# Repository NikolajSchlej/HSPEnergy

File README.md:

HSP Energy
=========

Hardware project of HS Regensburg

This project of Embedded Systems Laboratory of HS Regensburg 
aims to work out rules and guidelines for energy-effective coding
for different uC families.

There is a base board, where DC-DC, JTAG debugger and USB-UART converter are located, 
and CPU boards for different microcontrollers.

Documentation will be added when ready.

Scematics and layouts made in EagleCAD 6. 
All hardware involved is open and available under terms of copyleft license.

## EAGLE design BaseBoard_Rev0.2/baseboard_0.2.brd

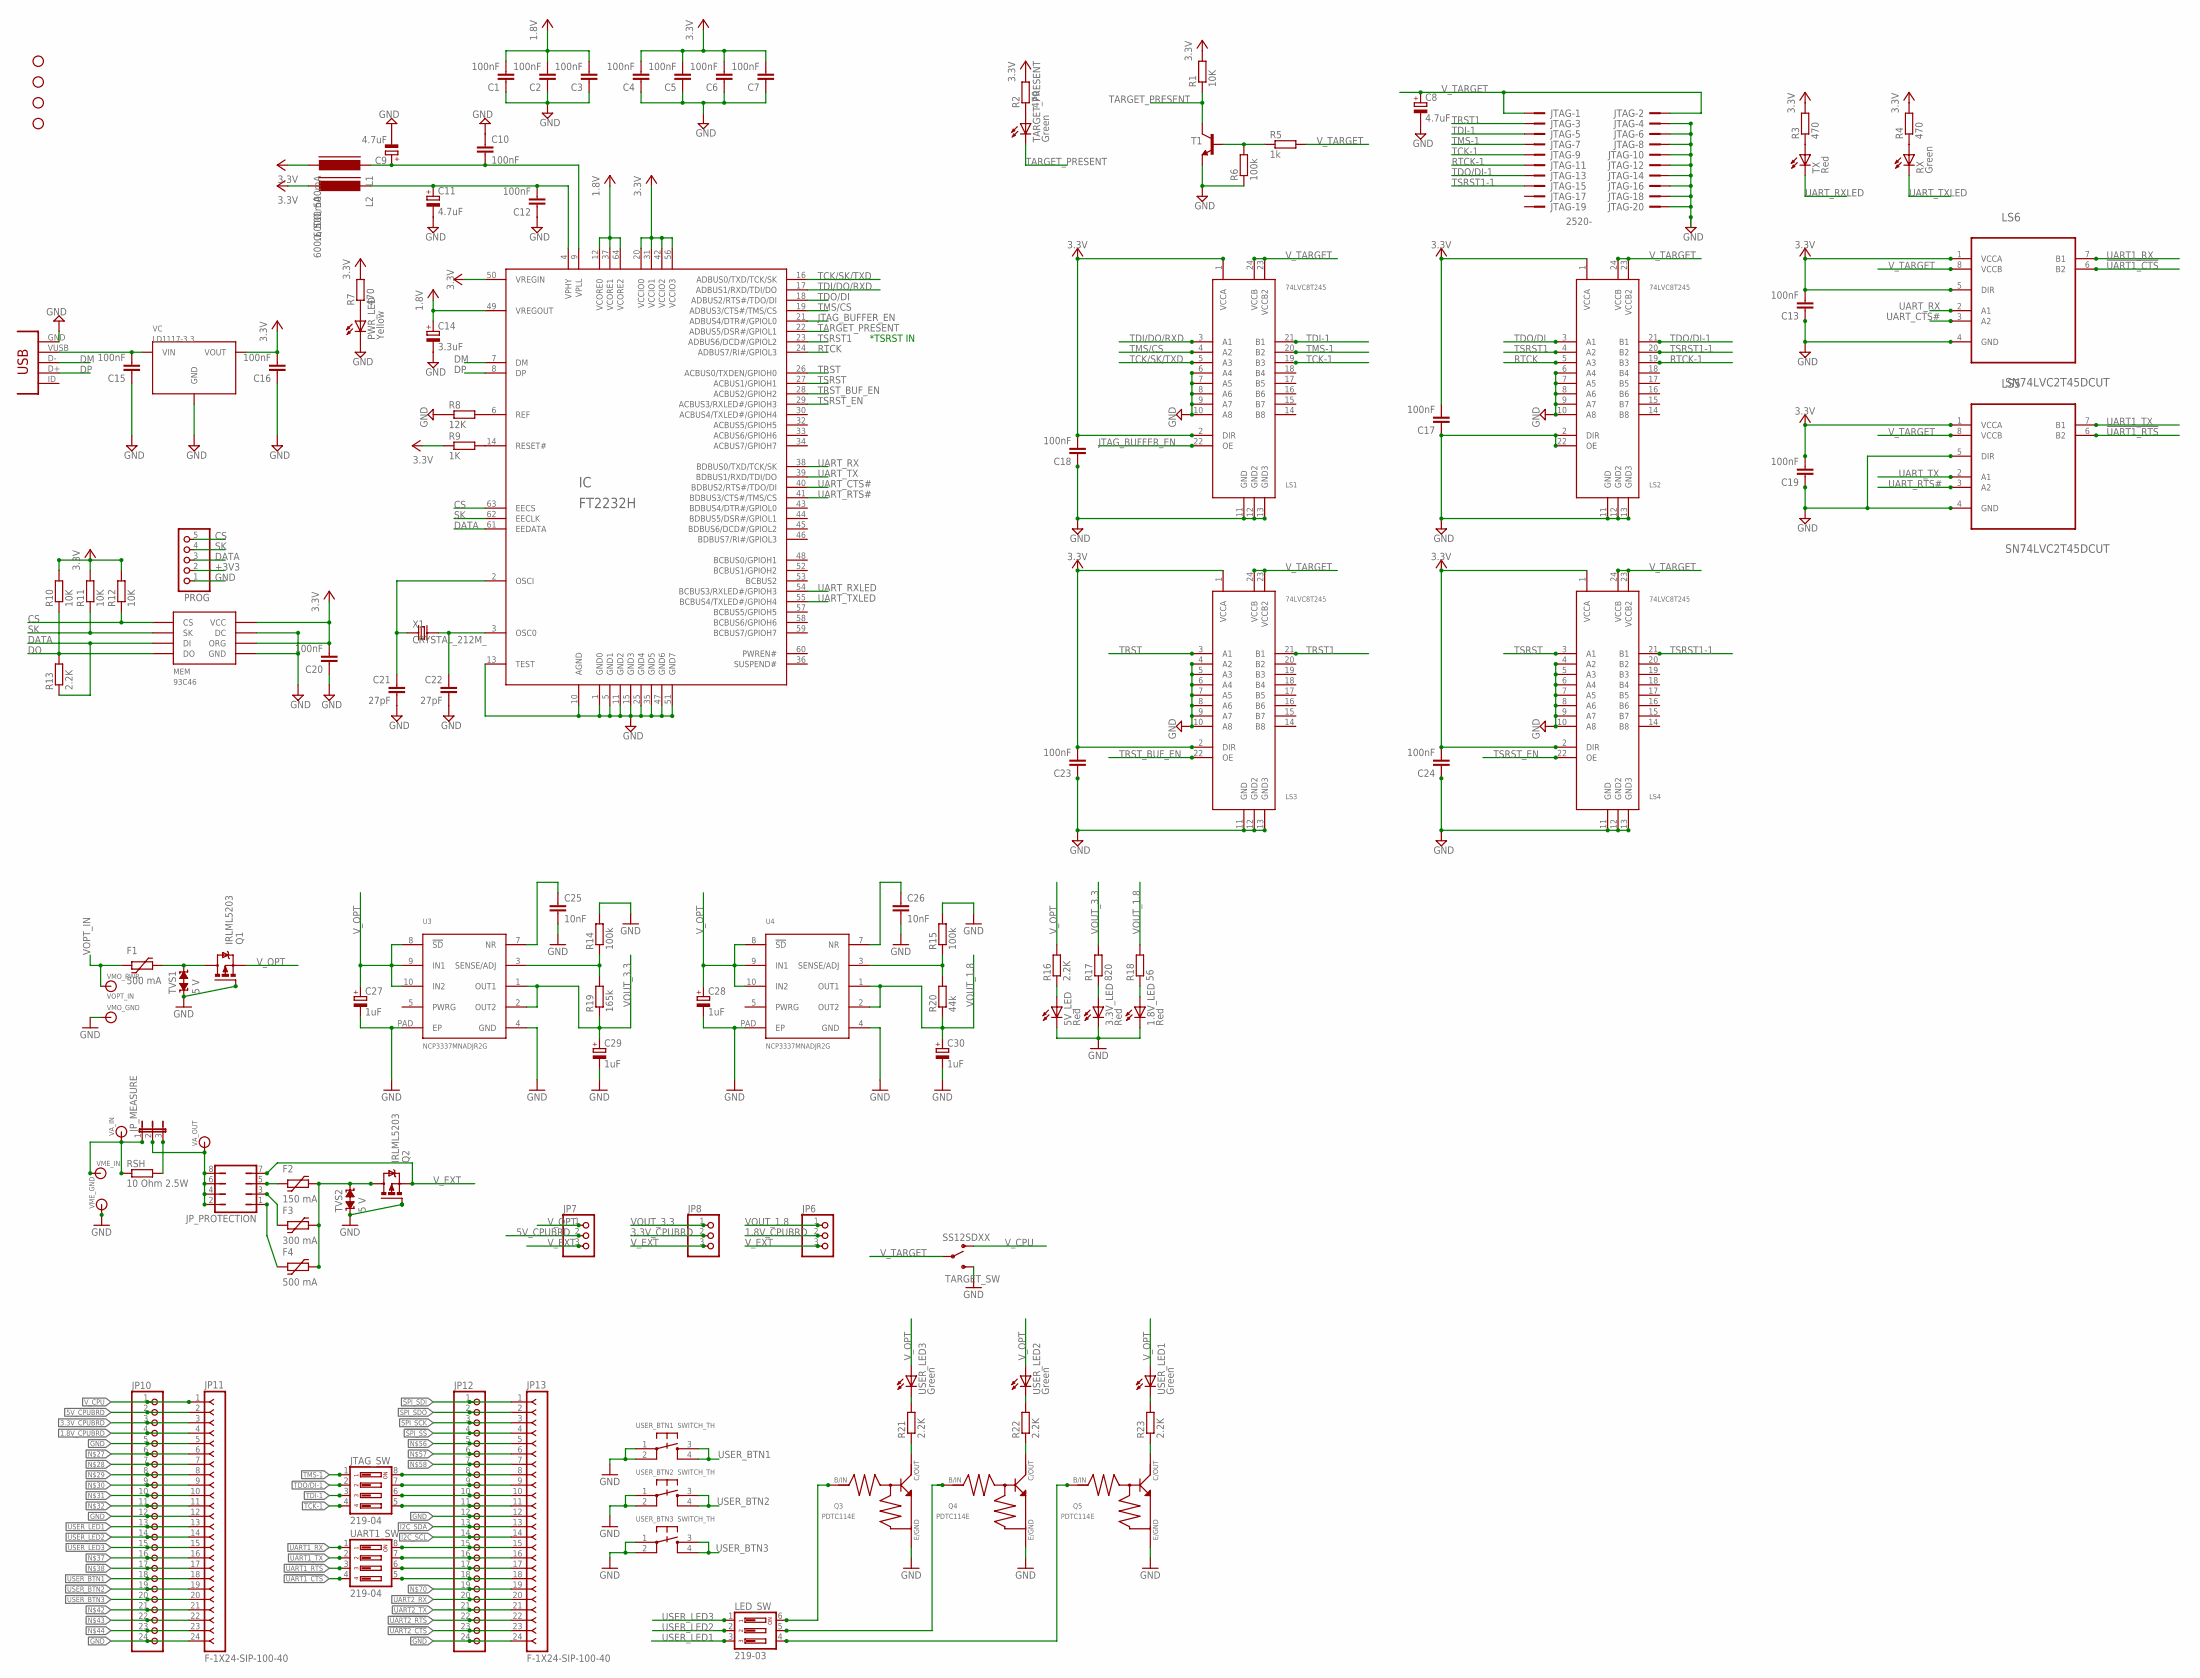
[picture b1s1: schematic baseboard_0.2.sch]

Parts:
1.8V_LED, 3.3V_LED, 5V_LED: Red; CHIPLED_0805
C1, C2, C3, C4, C5, C6, C7, C10, C12, C13, C15, C16, C17, C18, C19, C20, C23, C24: 100nF; C805
C8, C9, C11: 4.7uF; SMC_A
C14: 3.3uF; SMC_A
C21, C22: 27pF; C805
C25, C26: 10nF; C0805
C27, C28, C29, C30: 1uF; PANASONIC_B
CONN1: CONN_USB; CONN_USB_MINI-B
F1, F4: 500 mA; 1206L
F2: 150 mA; 1206L
F3: 300 mA; 1206L
IC: FT2232H; LQFP64
JP1, JP2, JP3, JP4: STAND-OFF
JP6, JP7, JP8: PINHD-1X3; 1X03
JP10, JP12: PINHD-1X24; 1X24
JP11, JP13: F-1X24-SIP-100-40; SIP-100-24-40
JP_MEASURE: JP2E; JP2
JP_PROTECTION: JP4Q
JTAG: 2520-; PAK100/2500-20
JTAG_SW: 219-04; CTS-219-04
L1, L2: 600Ω, 500mA; FB805
LED_SW: 219-03; CTS-219-03
LS1, LS2, LS3, LS4: 74LVC8T245; TSSOP24
LS5, LS6: SN74LVC2T45DCUT; SOP50P310X90-8N
MEM: 93C46; SOIC8
PROG: PINHD-1X5; 1X05
PWR_LED: Yellow; CHIPLED_0805
Q1, Q2: IRLML5203; MICRO3
Q3, Q4, Q5: PDTC114E; SOT416
R1, R10, R11, R12: 10K; R805
R2, R3, R4, R7: 470; R805
R5: 1k; R805
R6: 100k; R805
R8: 12K; R805
R9: 1K; R805
R13: 2.2K; R805
R14, R15: 100k; R0805
R16, R21, R22, R23: 2.2K; R0805
R17: 820; R0805
R18: 56; R0805
R19: 165k; R0805
R20: 44k; R0805
RSH: 10 Ohm 2.5W; R2512
RX: Green; CHIPLED_0805
T1: NPNSOT23BEC; SOT23-BEC
TARGET_PRESENT: Green; CHIPLED_0805
TARGET_SW: SS12SDXX
TVS1, TVS2: 5 V; TVS0805
TX: Red; CHIPLED_0805
U3, U4: NCP3337MNADJR2G; DFN10
UART1_SW: 219-04; CTS-219-04
USER_BTN1, USER_BTN2, USER_BTN3: SWITCH_TH; SWITCH_TROUGHHOLE
USER_LED1, USER_LED2, USER_LED3: Green; CHIPLED_0805
VA_IN: BANANA_CONN
VA_OUT: BANANA_CONN
VC: LD1117-3.3; SOT223
VME_GND: BANANA_CONN
VME_IN: BANANA_CONN
VMO_GND: BANANA_CONN
VMO_PWR: VOPT_IN; BANANA_CONN
X1: CRYSTAL_212M_; 4X6

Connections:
1.8V: C1.2, C2.2, C3.2, C14.+, IC.12 (VCORE0), IC.37 (VCORE1), IC.49 (VREGOUT), IC.64 (VCORE2)
1.8V_CPUBRD: JP6.2, JP10.4, JP11.4
3.3V_CPUBRD: JP8.2, JP10.3, JP11.3
5V_CPUBRD: JP7.2, JP10.2, JP11.2
!SPI_SS: JP12.4, JP13.4
!UART1_CTS: LS6.6 (B2), UART1_SW.4
!UART1_RTS: LS5.6 (B2), UART1_SW.3
!UART2_CTS: JP12.23, JP13.23
!UART2_RTS: JP12.22, JP13.22
+3V3: C4.2, C5.2, C6.2, C7.2, C13.2, C16.2, C17.2, C18.2, C19.2, C20.2, C23.2, C24.2, IC.20 (VCCIO0), IC.31 (VCCIO1), IC.42 (VCCIO2), IC.50 (VREGIN), IC.56 (VCCIO3), L1.2, L2.2, LS1.1 (VCCA), LS1.2 (DIR), LS2.1 (VCCA), LS3.1 (VCCA), LS3.2 (DIR), LS4.1 (VCCA), LS4.2 (DIR), LS5.1 (VCCA), LS6.1 (VCCA), LS6.5 (DIR), MEM.6 (ORG), MEM.8 (VCC), PROG.2, R1.2, R2.2, R3.2, R4.2, R7.2, R9.1, R10.2, R11.2, R12.2, VC.2 (VOUT)
CS: IC.63 (EECS), MEM.1 (CS), PROG.5, R12.1
DATA: IC.61 (EEDATA), MEM.3 (DI), PROG.3, R13.1
DM: CONN1.D-, IC.7 (DM)
DO: MEM.4 (DO), R10.1, R13.2
DP: CONN1.D+, IC.8 (DP)
GND: 1.8V_LED.C, 3.3V_LED.C, 5V_LED.C, C1.1, C2.1, C3.1, C4.1, C5.1, C6.1, C7.1, C8.-, C9.-, C10.1, C11.-, C12.1, C13.1, C14.-, C15.1, C16.1, C17.1, C18.1, C19.1, C20.1, C21.2, C22.2, C23.1, C24.1, C25.2, C26.2, C27.-, C28.-, C29.-, C30.-, CONN1.GND, IC.1 (GND0), IC.5 (GND1), IC.10 (AGND), IC.11 (GND2), IC.13 (TEST), IC.15 (GND3), IC.25 (GND4), IC.35 (GND5), IC.47 (GND6), IC.51 (GND7), JP10.5, JP10.12, JP10.24, JP11.5, JP11.12, JP11.24, JP12.12, JP12.24, JP13.12, JP13.24, JTAG.4, JTAG.6, JTAG.8, JTAG.10, JTAG.12, JTAG.14, JTAG.16, JTAG.18, JTAG.20, LS1.6 (A4), LS1.7 (A5), LS1.8 (A6), LS1.9 (A7), LS1.10 (A8), LS1.11 (GND), LS1.12 (GND2), LS1.13 (GND3), LS2.2 (DIR), LS2.6 (A4), LS2.7 (A5), LS2.8 (A6), LS2.9 (A7), LS2.10 (A8), LS2.11 (GND), LS2.12 (GND2), LS2.13 (GND3), LS2.22 (OE), LS3.4 (A2), LS3.5 (A3), LS3.6 (A4), LS3.7 (A5), LS3.8 (A6), LS3.9 (A7), LS3.10 (A8), LS3.11 (GND), LS3.12 (GND2), LS3.13 (GND3), LS4.4 (A2), LS4.5 (A3), LS4.6 (A4), LS4.7 (A5), LS4.8 (A6), LS4.9 (A7), LS4.10 (A8), LS4.11 (GND), LS4.12 (GND2), LS4.13 (GND3), LS5.4 (GND), LS5.5 (DIR), LS6.4 (GND), MEM.5 (GND), MEM.7 (DC), PROG.1, PWR_LED.C, Q1.1 (G), Q2.1 (G), Q3.2 (E), Q4.2 (E), Q5.2 (E), R6.1, R8.1, R14.2, R15.2, T1.E, TARGET_SW.3, TVS1.1, TVS2.1, U3.4 (GND), U3.PAD (EP), U4.4 (GND), U4.PAD (EP), USER_BTN1.1, USER_BTN1.2, USER_BTN2.1, USER_BTN2.2, USER_BTN3.1, USER_BTN3.2, VC.1 (GND), VME_GND.P$1, VMO_GND.P$1
I2C_SCL: JP12.14, JP13.14
I2C_SDA: JP12.13, JP13.13
JTAG_BUFFER_EN: IC.21 (ADBUS4/DTR#/GPIOL0), LS1.22 (OE)
JTAG_TCK: JP12.11, JP13.11, JTAG_SW.5
JTAG_TDI: JP12.10, JP13.10, JTAG_SW.6
JTAG_TDO: JP12.9, JP13.9, JTAG_SW.7
JTAG_TMS: JP12.8, JP13.8, JTAG_SW.8
unnamed: LED_SW.6, Q3.1 (B)
unnamed: C22.1, IC.3 (OSC0), X1.2 (X2)
unnamed: F2.P$1 (1), JP_PROTECTION.5
unnamed: F3.P$1 (1), JP_PROTECTION.3
unnamed: F4.P$1 (1), JP_PROTECTION.1
unnamed: F2.P$2 (2), F3.P$2 (2), F4.P$2 (2), Q2.3 (D), TVS2.2
unnamed: C21.1, IC.2 (OSCI), X1.1 (X1)
unnamed: C15.2, CONN1.VUSB, VC.3 (VIN)
unnamed: IC.14 (RESET#), R9.2
unnamed: IC.6 (REF), R8.2
unnamed: 3.3V_LED.A, R17.1
unnamed: R5.1, R6.2, T1.B
unnamed: PWR_LED.A, R7.1
unnamed: R2.1, TARGET_PRESENT.A
unnamed: F1.P$2 (2), Q1.3 (D), TVS1.2
unnamed: 5V_LED.A, R16.1
unnamed: R4.1, RX.A
unnamed: R3.1, TX.A
unnamed: LED_SW.4, Q5.1 (B)
unnamed: 1.8V_LED.A, R18.1
unnamed: JP10.6, JP11.6
unnamed: JP10.7, JP11.7
unnamed: JP10.8, JP11.8
unnamed: JP10.9, JP11.9
unnamed: JP10.10, JP11.10
unnamed: JP10.11, JP11.11
unnamed: JP_MEASURE.1, RSH.1, VA_IN.P$1, VME_IN.P$1
unnamed: JP_MEASURE.3, RSH.2
unnamed: JP10.16, JP11.16
unnamed: JP10.17, JP11.17
unnamed: JP10.21, JP11.21
unnamed: JP10.22, JP11.22
unnamed: JP10.23, JP11.23
unnamed: C25.1, U3.7 (NR)
unnamed: JP12.5, JP13.5
unnamed: JP12.6, JP13.6
unnamed: JP12.7, JP13.7
unnamed: Q3.3 (C), R21.1
unnamed: R21.2, USER_LED3.C
unnamed: R22.2, USER_LED2.C
unnamed: R23.2, USER_LED1.C
unnamed: Q4.3 (C), R22.1
unnamed: JP12.15, JP13.15, UART1_SW.8
unnamed: JP12.16, JP13.16, UART1_SW.7
unnamed: JP12.17, JP13.17, UART1_SW.6
unnamed: JP12.18, JP13.18, UART1_SW.5
unnamed: JP12.19, JP13.19
unnamed: R14.1, R19.2, U3.3 (SENSE/ADJ)
unnamed: Q5.3 (C), R23.1
unnamed: C26.1, U4.7 (NR)
unnamed: LED_SW.5, Q4.1 (B)
unnamed: R15.1, R20.2, U4.3 (SENSE/ADJ)
RTCK: IC.24 (ADBUS7/RI#/GPIOL3), LS2.5 (A3)
RTCK-1: JTAG.11, LS2.19 (B3)
SK: IC.62 (EECLK), MEM.2 (SK), PROG.4, R11.1
SPI_SCK: JP12.3, JP13.3
SPI_SDI: JP12.1, JP13.1
SPI_SDO: JP12.2, JP13.2
TARGET_PRESENT: IC.22 (ADBUS5/DSR#/GPIOL1), R1.1, T1.C, TARGET_PRESENT.C
TCK-1: JTAG.9, JTAG_SW.4, LS1.19 (B3)
TCK/SK/TXD: IC.16 (ADBUS0/TXD/TCK/SK), LS1.5 (A3)
TDI-1: JTAG.5, JTAG_SW.3, LS1.21 (B1)
TDI/DO/RXD: IC.17 (ADBUS1/RXD/TDI/DO), LS1.3 (A1)
TDO/DI: IC.18 (ADBUS2/RTS#/TDO/DI), LS2.3 (A1)
TDO/DI-1: JTAG.13, JTAG_SW.2, LS2.21 (B1)
TMS-1: JTAG.7, JTAG_SW.1, LS1.20 (B2)
TMS/CS: IC.19 (ADBUS3/CTS#/TMS/CS), LS1.4 (A2)
TRST: IC.26 (ACBUS0/TXDEN/GPIOH0), LS3.3 (A1)
TRST1: JTAG.3, LS3.21 (B1)
TRST_BUF_EN: IC.28 (ACBUS2/GPIOH2), LS3.22 (OE)
TSRST: IC.27 (ACBUS1/GPIOH1), LS4.3 (A1)
TSRST1: IC.23 (ADBUS6/DCD#/GPIOL2), LS2.4 (A2)
TSRST1-1: JTAG.15, LS2.20 (B2), LS4.21 (B1)
TSRST_EN: IC.29 (ACBUS3/RXLED#/GPIOH3), LS4.22 (OE)
UART1_RX: LS6.7 (B1), UART1_SW.1
UART1_TX: LS5.7 (B1), UART1_SW.2
UART2_RX: JP12.20, JP13.20
UART2_TX: JP12.21, JP13.21
UART_CTS#: IC.40 (BDBUS2/RTS#/TDO/DI), LS6.3 (A2)
UART_RTS#: IC.41 (BDBUS3/CTS#/TMS/CS), LS5.3 (A2)
UART_RX: IC.38 (BDBUS0/TXD/TCK/SK), LS6.2 (A1)
UART_RXLED: IC.54 (BCBUS3/RXLED#/GPIOH3), TX.C
UART_TX: IC.39 (BDBUS1/RXD/TDI/DO), LS5.2 (A1)
UART_TXLED: IC.55 (BCBUS4/TXLED#/GPIOH4), RX.C
USER_BTN1: JP10.18, JP11.18, USER_BTN1.3, USER_BTN1.4
USER_BTN2: JP10.19, JP11.19, USER_BTN2.3, USER_BTN2.4
USER_BTN3: JP10.20, JP11.20, USER_BTN3.3, USER_BTN3.4
USER_LED1: JP10.13, JP11.13, LED_SW.3
USER_LED2: JP10.14, JP11.14, LED_SW.2
USER_LED3: JP10.15, JP11.15, LED_SW.1
VEXT_IN: JP_MEASURE.2, JP_PROTECTION.2, JP_PROTECTION.4, JP_PROTECTION.6, JP_PROTECTION.8, VA_OUT.P$1
VOPT_IN: F1.P$1 (1), VMO_PWR.P$1
VOUT_1.8: C30.+, JP6.1, R18.2, R20.1, U4.1 (OUT1), U4.2 (OUT2)
VOUT_3.3: C29.+, JP8.1, R17.2, R19.1, U3.1 (OUT1), U3.2 (OUT2)
VPHY: C11.+, C12.2, IC.4 (VPHY), L2.1
VPLL: C9.+, C10.2, IC.9 (VPLL), L1.1
V_CPU: JP10.1, JP11.1, TARGET_SW.1
V_EXT: JP6.3, JP7.3, JP8.3, JP_PROTECTION.7, Q2.2 (S)
V_OPT: C27.+, C28.+, JP7.1, Q1.2 (S), R16.2, U3.8 (!SD), U3.9 (IN1), U3.10 (IN2), U4.8 (!SD), U4.9 (IN1), U4.10 (IN2), USER_LED1.A, USER_LED2.A, USER_LED3.A
V_TARGET: C8.+, JTAG.1, JTAG.2, LS1.23 (VCCB2), LS1.24 (VCCB), LS2.23 (VCCB2), LS2.24 (VCCB), LS3.23 (VCCB2), LS3.24 (VCCB), LS4.23 (VCCB2), LS4.24 (VCCB), LS5.8 (VCCB), LS6.8 (VCCB), R5.2, TARGET_SW.2

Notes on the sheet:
*TSRST IN

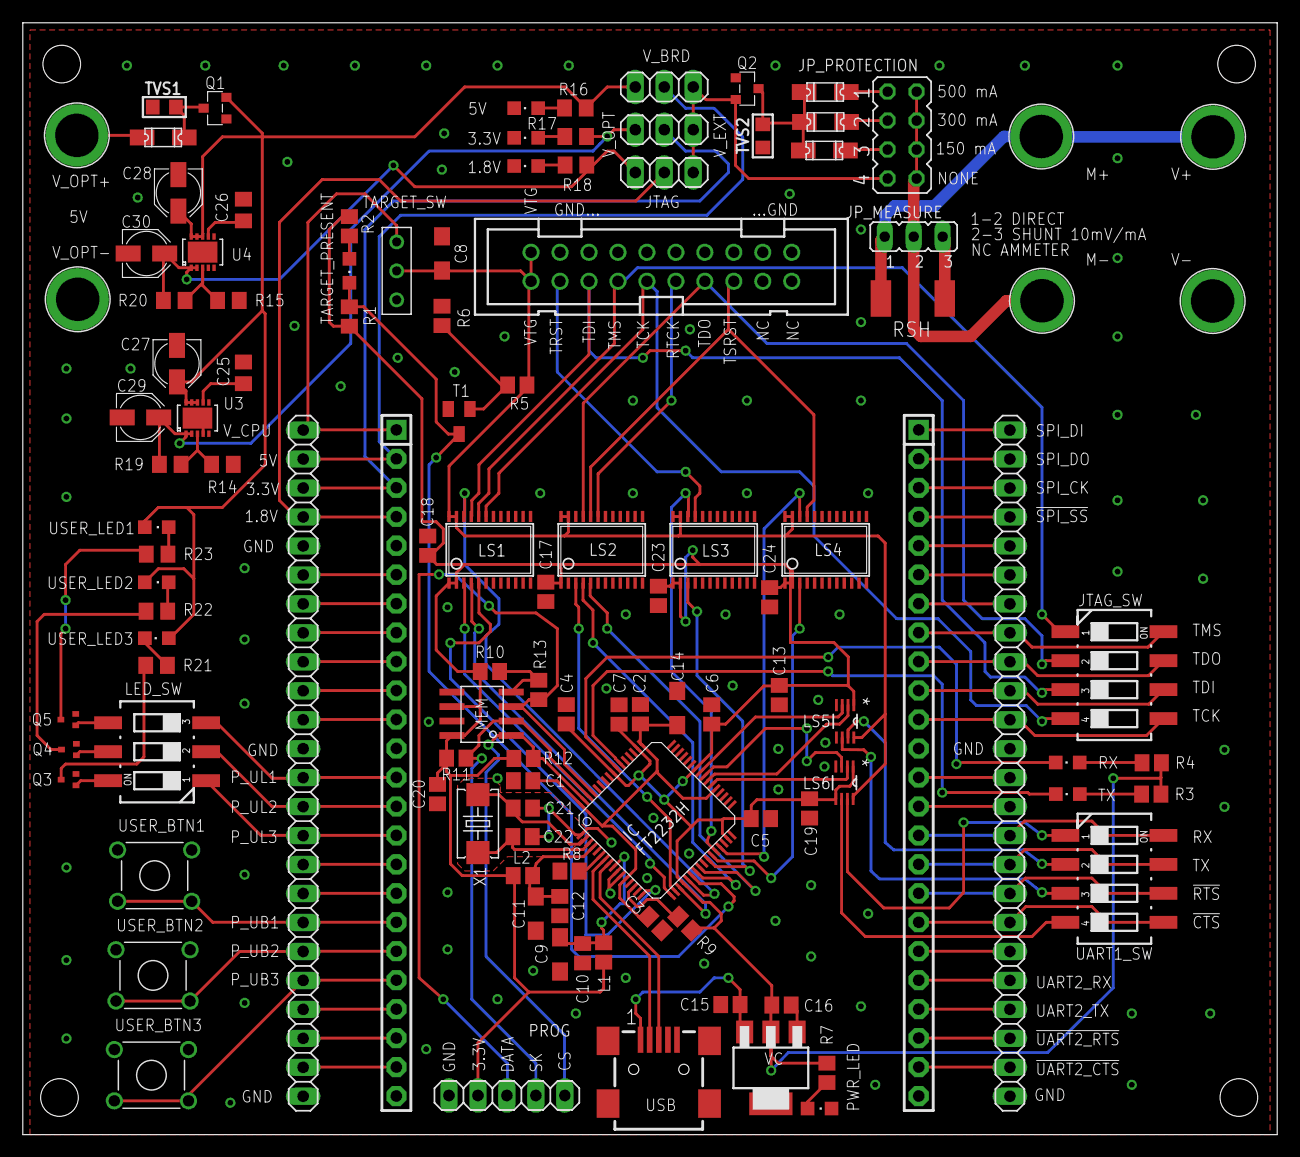
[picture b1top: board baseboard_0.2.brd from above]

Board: 2 copper layers, 110.0 x 97.5 mm, 119 parts (0 on the bottom side), 123 nets.

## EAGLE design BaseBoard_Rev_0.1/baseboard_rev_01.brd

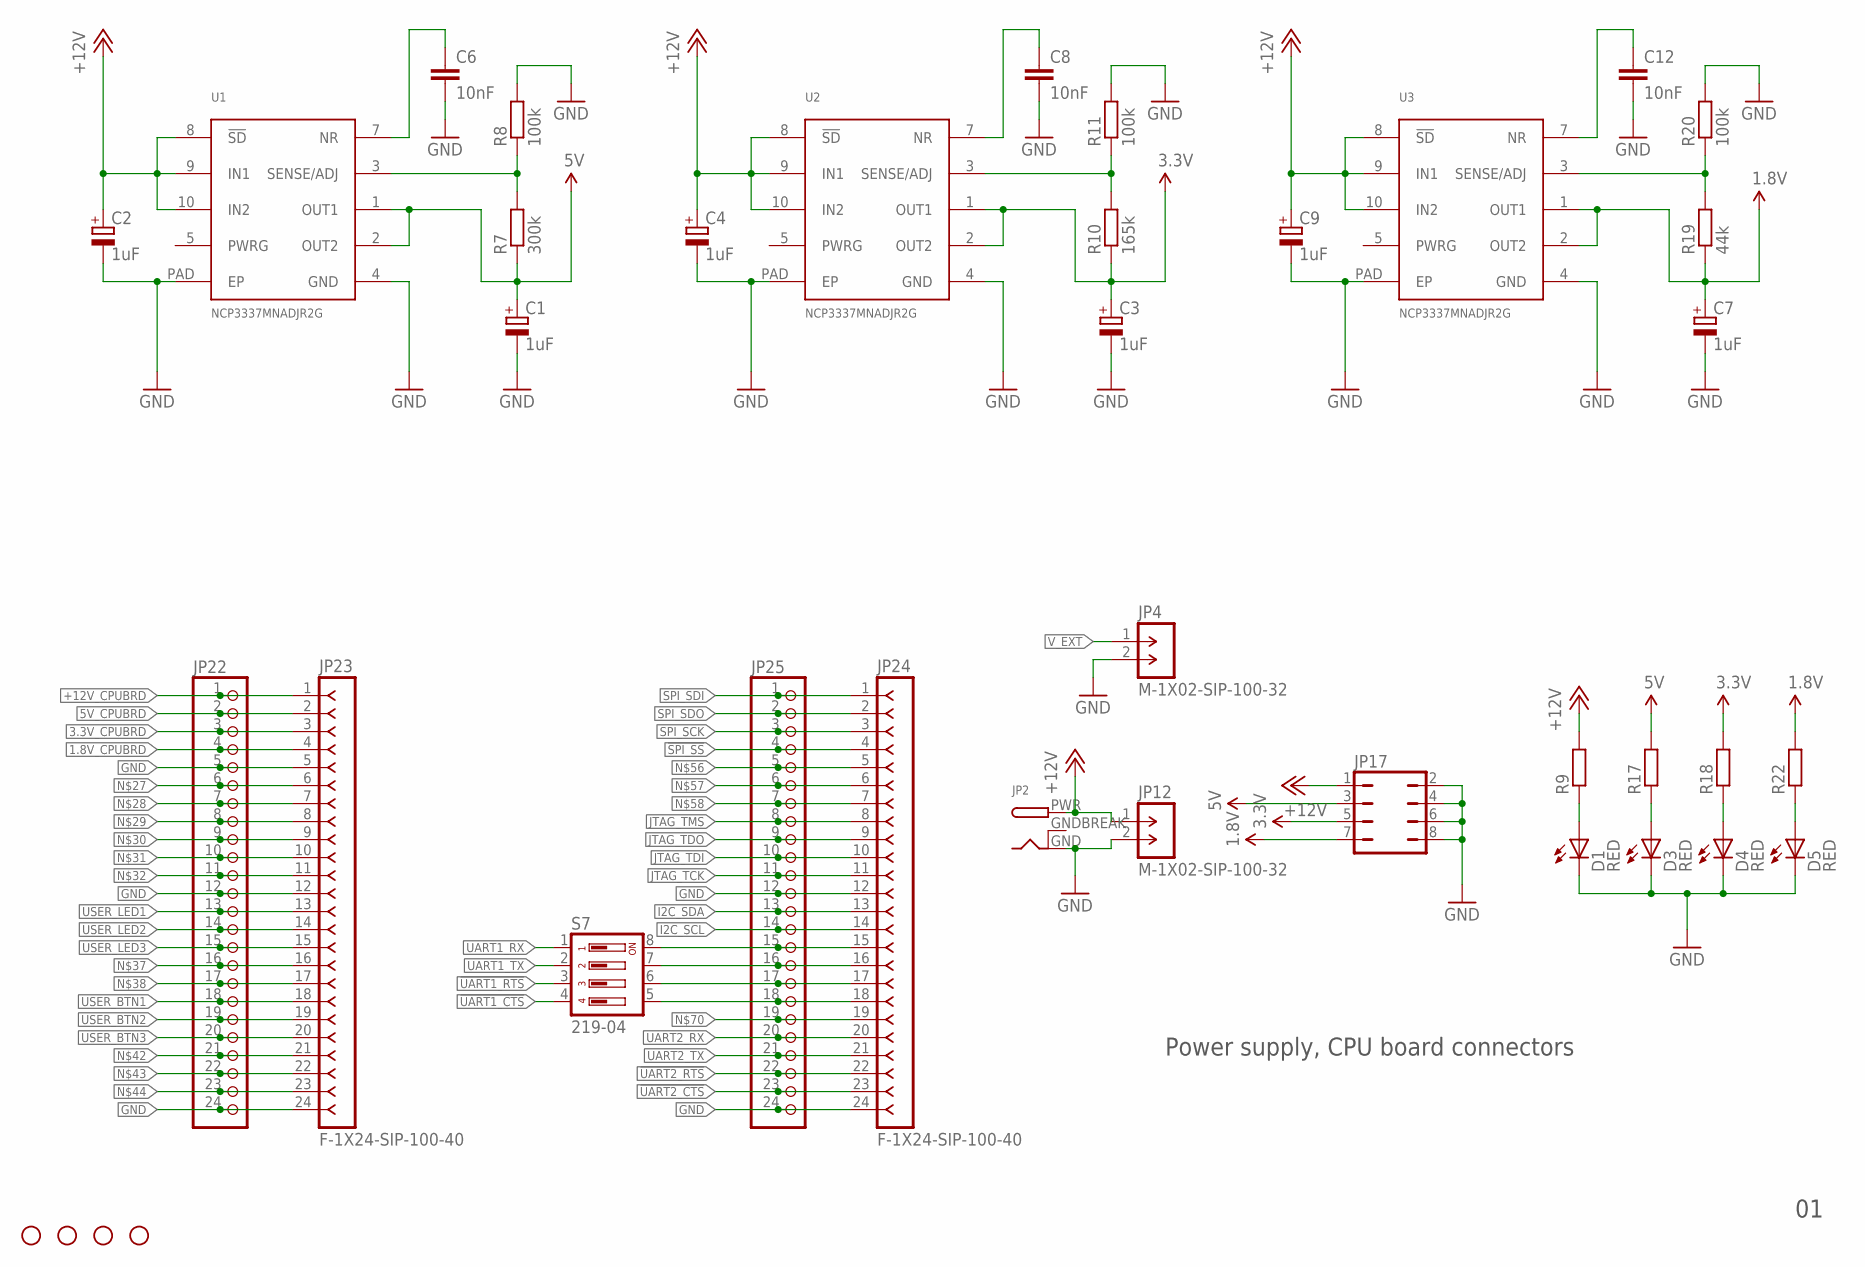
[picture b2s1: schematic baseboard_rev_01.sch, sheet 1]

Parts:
C1, C2, C3, C4, C7, C9: 1uF; PANASONIC_B
C6, C8, C12: 10nF; C0805
D1, D3, D4, D5: RED; CHIPLED_0805
JP1, JP11, JP26, JP28: STAND-OFF
JP2: DCBARRELPTH; DCJACK_2MM_PTH
JP4, JP12: M-1X02-SIP-100-32; SIP-100-02-32
JP17: JP4Q
JP22, JP25: PINHD-1X24; 1X24
JP23, JP24: F-1X24-SIP-100-40; SIP-100-24-40
R7: 300k; R0805
R8, R11, R20: 100k; R0805
R9, R17, R18, R22: R-EU_R0805; R0805
R10: 165k; R0805
R19: 44k; R0805
S7: 219-04; CTS-219-04
U1, U2, U3: NCP3337MNADJR2G; DFN10

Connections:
1.8V: C7.+, JP17.7, R19.1, R22.2, U3.1 (OUT1), U3.2 (OUT2); also elsewhere on the board
1.8V_CPUBRD: JP22.4, JP23.4; also elsewhere on the board
3.3V: C3.+, JP17.5, R10.1, R18.2, U2.1 (OUT1), U2.2 (OUT2); also elsewhere on the board
3.3V_CPUBRD: JP22.3, JP23.3; also elsewhere on the board
5V: C1.+, JP17.3, R7.1, R17.2, U1.1 (OUT1), U1.2 (OUT2); also elsewhere on the board
5V_CPUBRD: JP22.2, JP23.2; also elsewhere on the board
!SPI_SS: JP24.4, JP25.4
!UART1_CTS: S7.4; also elsewhere on the board
!UART1_RTS: S7.3; also elsewhere on the board
!UART2_CTS: JP24.23, JP25.23
!UART2_RTS: JP24.22, JP25.22
+12V: C2.+, C4.+, C9.+, JP2.PWR, JP12.1, JP17.1, R9.2, U1.8 (!SD), U1.9 (IN1), U1.10 (IN2), U2.8 (!SD), U2.9 (IN1), U2.10 (IN2), U3.8 (!SD), U3.9 (IN1), U3.10 (IN2); also elsewhere on the board
+12V_CPUBRD: JP22.1, JP23.1; also elsewhere on the board
GND: C1.-, C2.-, C3.-, C4.-, C6.2, C7.-, C8.2, C9.-, C12.2, D1.C, D3.C, D4.C, D5.C, JP2.GND, JP4.2, JP12.2, JP17.2, JP17.4, JP17.6, JP17.8, JP22.5, JP22.12, JP22.24, JP23.5, JP23.12, JP23.24, JP24.12, JP24.24, JP25.12, JP25.24, R8.2, R11.2, R20.2, U1.4 (GND), U1.PAD (EP), U2.4 (GND), U2.PAD (EP), U3.4 (GND), U3.PAD (EP); also elsewhere on the board
GNDBREAK: JP2.GNDBREAK
I2C_SCL: JP24.14, JP25.14
I2C_SDA: JP24.13, JP25.13
JTAG_TCK: JP24.11, JP25.11
JTAG_TDI: JP24.10, JP25.10
JTAG_TDO: JP24.9, JP25.9
JTAG_TMS: JP24.8, JP25.8
unnamed: D4.A, R18.1
unnamed: D3.A, R17.1
unnamed: D1.A, R9.1
unnamed: D5.A, R22.1
unnamed: JP22.6, JP23.6
unnamed: JP22.7, JP23.7
unnamed: JP22.8, JP23.8
unnamed: JP22.9, JP23.9
unnamed: JP22.10, JP23.10
unnamed: JP22.11, JP23.11
unnamed: JP22.16, JP23.16
unnamed: JP22.17, JP23.17
unnamed: JP22.21, JP23.21
unnamed: JP22.22, JP23.22
unnamed: JP22.23, JP23.23
unnamed: C8.1, U2.7 (NR)
unnamed: JP24.5, JP25.5
unnamed: JP24.6, JP25.6
unnamed: JP24.7, JP25.7
unnamed: JP24.15, JP25.15, S7.8
unnamed: JP24.16, JP25.16, S7.7
unnamed: JP24.17, JP25.17, S7.6
unnamed: JP24.18, JP25.18, S7.5
unnamed: JP24.19, JP25.19
unnamed: R10.2, R11.1, U2.3 (SENSE/ADJ)
unnamed: C6.1, U1.7 (NR)
unnamed: R7.2, R8.1, U1.3 (SENSE/ADJ)
unnamed: C12.1, U3.7 (NR)
unnamed: R19.2, R20.1, U3.3 (SENSE/ADJ)
SPI_SCK: JP24.3, JP25.3
SPI_SDI: JP24.1, JP25.1
SPI_SDO: JP24.2, JP25.2
UART1_RX: S7.1; also elsewhere on the board
UART1_TX: S7.2; also elsewhere on the board
UART2_RX: JP24.20, JP25.20
UART2_TX: JP24.21, JP25.21
USER_BTN1: JP22.18, JP23.18; also elsewhere on the board
USER_BTN2: JP22.19, JP23.19; also elsewhere on the board
USER_BTN3: JP22.20, JP23.20; also elsewhere on the board
USER_LED1: JP22.13, JP23.13; also elsewhere on the board
USER_LED2: JP22.14, JP23.14; also elsewhere on the board
USER_LED3: JP22.15, JP23.15; also elsewhere on the board
V_EXT: JP4.1; also elsewhere on the board

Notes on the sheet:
Power supply, CPU board connectors

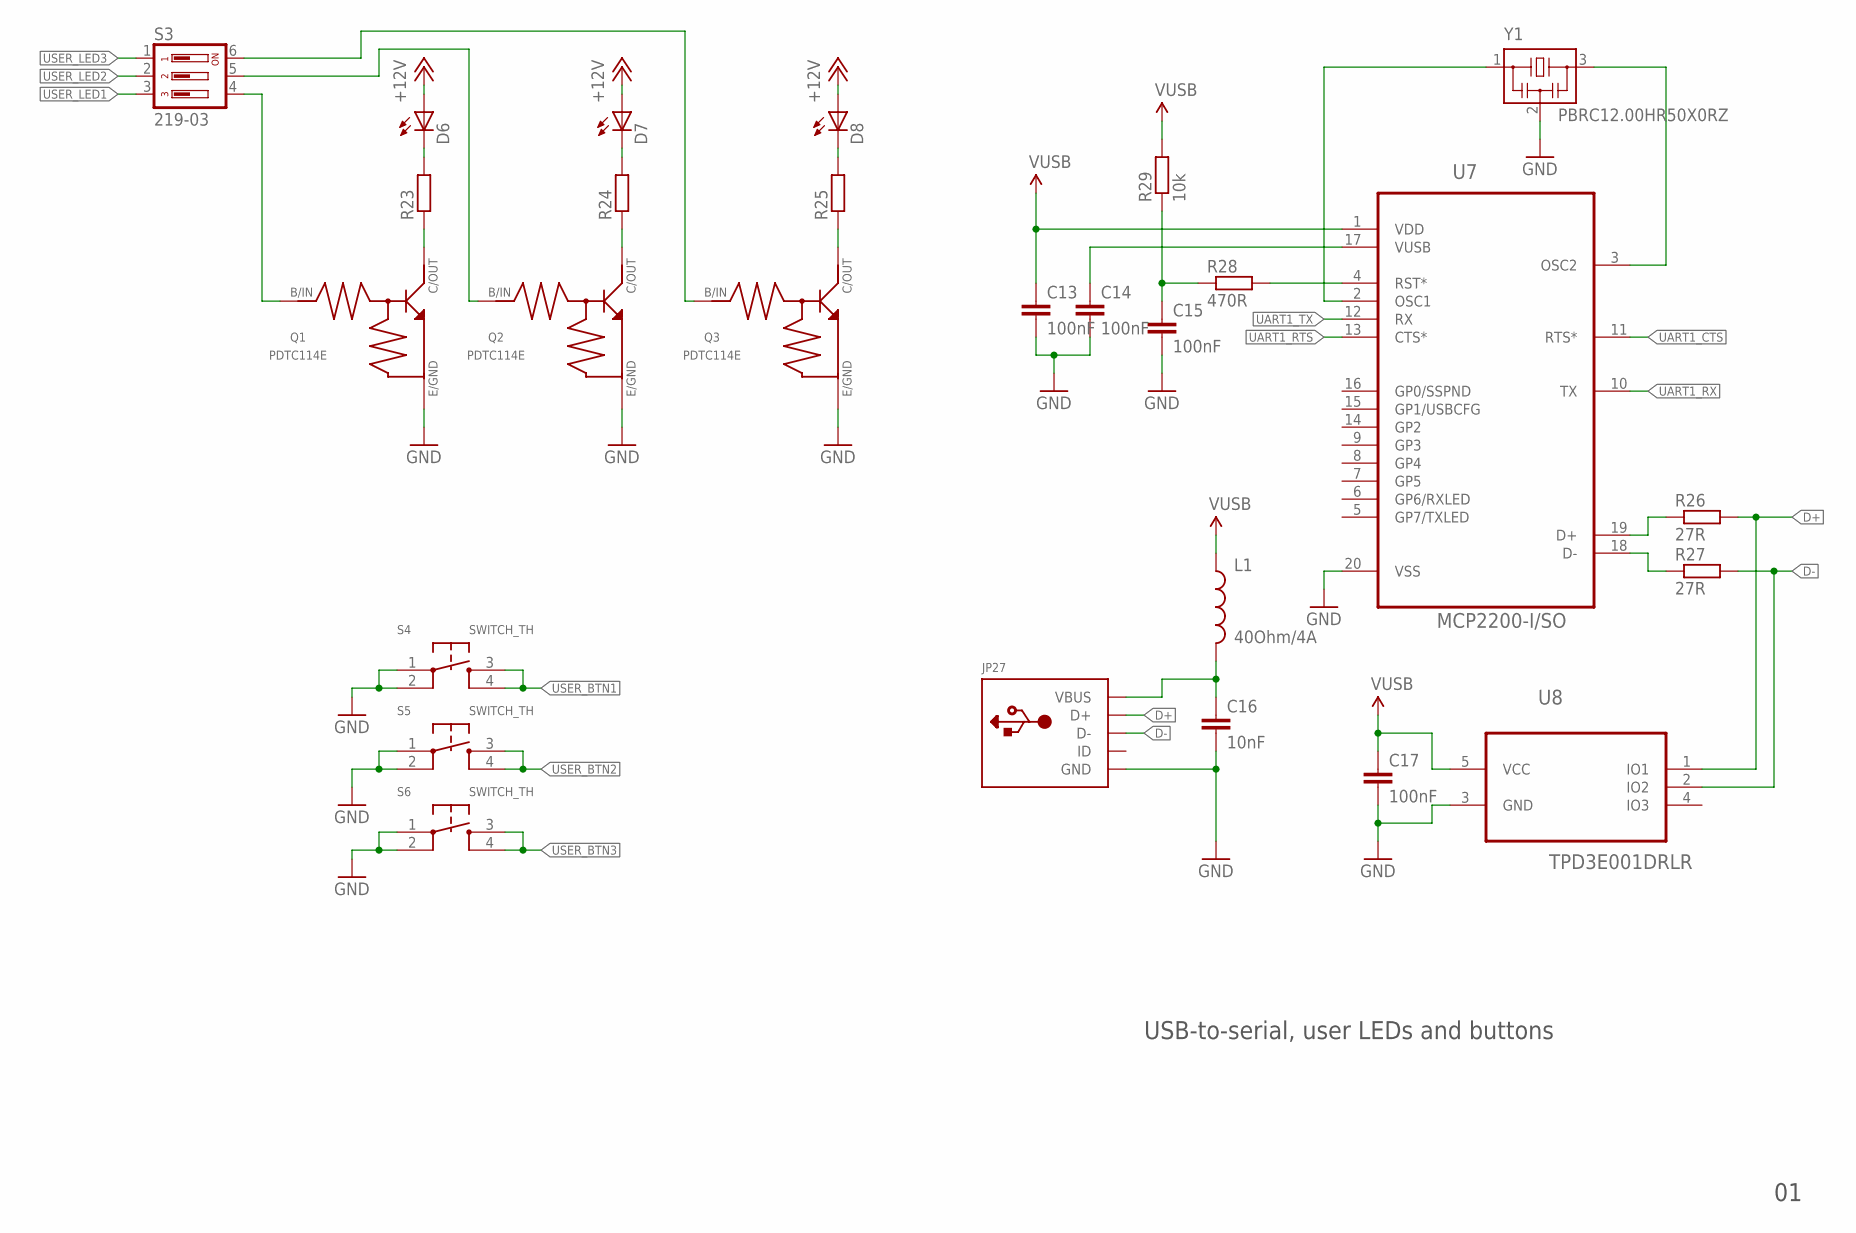
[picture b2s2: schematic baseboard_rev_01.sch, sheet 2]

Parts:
C13, C14, C15, C17: 100nF; C0805
C16: 10nF; C0805
D6, D7, D8: LEDCHIPLED_0805; CHIPLED_0805
JP27: USBMINIB; USB-MINIB
L1: 40Ohm/4A; 0805
Q1, Q2, Q3: PDTC114E; SOT416
R23, R24, R25: R-EU_R0805; R0805
R26, R27: 27R; R0805
R28: 470R; R0805
R29: 10k; R0805
S3: 219-03; CTS-219-03
S4, S5, S6: SWITCH_TH; SWITCH_TROUGHHOLE
U7: MCP2200-I/SO; SOIC127P1034X264-20N
U8: TPD3E001DRLR; SOT50P160X60-5N
Y1: PBRC12.00HR50X0RZ; PBRC-H

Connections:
!UART1_CTS: U7.11 (RTS*); also elsewhere on the board
!UART1_RTS: U7.13 (CTS*); also elsewhere on the board
+12V: D6.A, D7.A, D8.A; also elsewhere on the board
D+: JP27.D+, R26.2, U8.1 (IO1)
D-: JP27.D-, R27.2, U8.2 (IO2)
GND: C13.2, C14.2, C15.2, C16.2, C17.2, JP27.GND, Q1.2 (E), Q2.2 (E), Q3.2 (E), S4.1, S4.2, S5.1, S5.2, S6.1, S6.2, U7.20 (VSS), U8.3 (GND), Y1.2; also elsewhere on the board
unnamed: Q3.1 (B), S3.6
unnamed: Q2.1 (B), S3.5
unnamed: Q1.1 (B), S3.4
unnamed: Q1.3 (C), R23.1
unnamed: D6.C, R23.2
unnamed: D7.C, R24.2
unnamed: D8.C, R25.2
unnamed: Q2.3 (C), R24.1
unnamed: Q3.3 (C), R25.1
unnamed: C16.1, JP27.VBUS, L1.2
unnamed: C15.1, R28.1, R29.1
unnamed: R28.2, U7.4 (RST*)
unnamed: U7.2 (OSC1), Y1.1
unnamed: C14.1, U7.17 (VUSB)
unnamed: U7.3 (OSC2), Y1.3
unnamed: R26.1, U7.19 (D+)
unnamed: R27.1, U7.18 (D-)
UART1_RX: U7.10 (TX); also elsewhere on the board
UART1_TX: U7.12 (RX); also elsewhere on the board
USER_BTN1: S4.3, S4.4; also elsewhere on the board
USER_BTN2: S5.3, S5.4; also elsewhere on the board
USER_BTN3: S6.3, S6.4; also elsewhere on the board
USER_LED1: S3.3; also elsewhere on the board
USER_LED2: S3.2; also elsewhere on the board
USER_LED3: S3.1; also elsewhere on the board
VUSB: C13.1, C17.1, L1.1, R29.2, U7.1 (VDD), U8.5 (VCC)

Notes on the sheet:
USB-to-serial, user LEDs and buttons

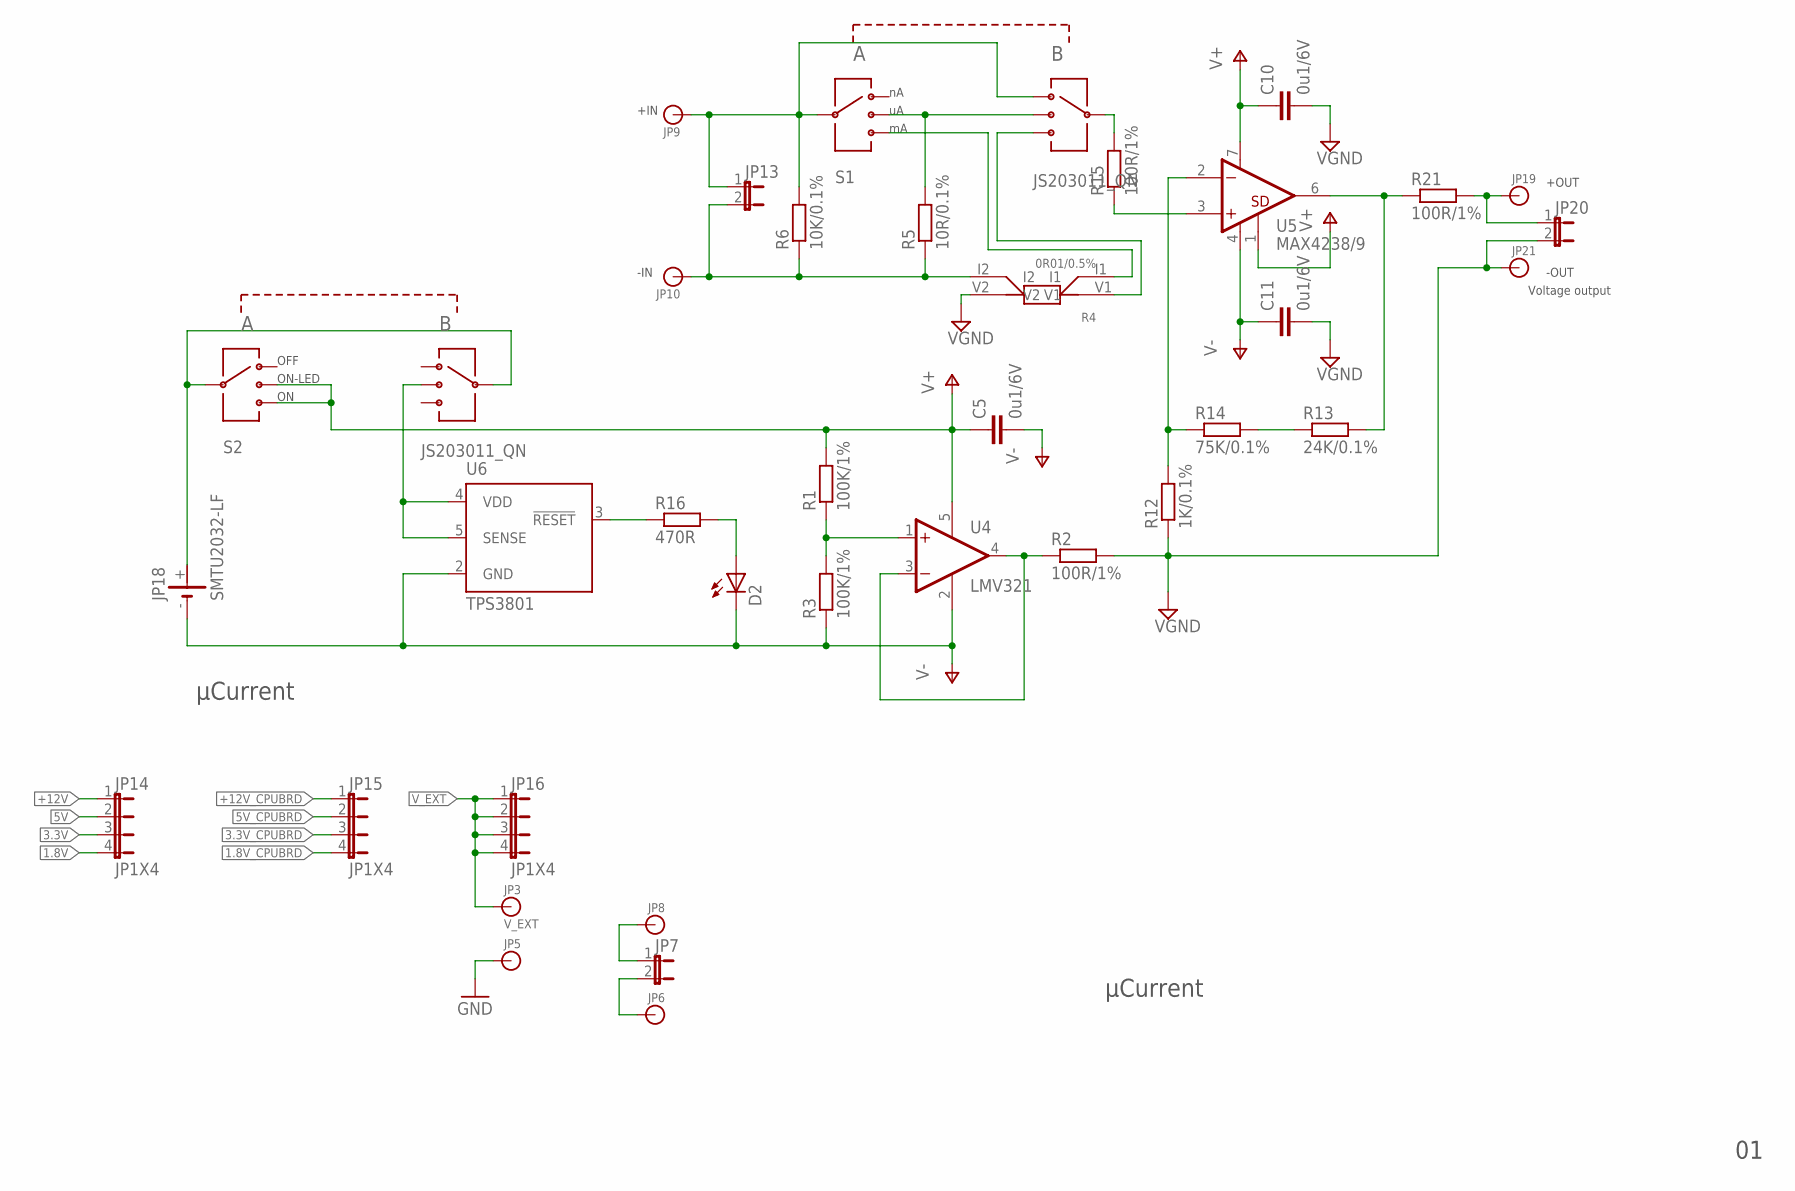
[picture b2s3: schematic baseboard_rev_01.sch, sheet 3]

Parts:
C5, C10, C11: 0u1/6V; C0805K
D2: LEDCHIPLED_0805; CHIPLED_0805
JP3: V_EXT; BANANA_CONN
JP5, JP6, JP8, JP9, JP10, JP19, JP21: BANANA_CONN
JP7, JP13, JP20: JUMPER-2PTH; 1X02
JP14, JP15, JP16: JP1X4
JP18: SMTU2032-LF
R1, R3: 100K/1%; R0805
R2, R15, R21: 100R/1%; R0805
R4: 0R01/0.5%; LVK12RXXXXXX
R5: 10R/0.1%; R0805
R6: 10K/0.1%; R0805
R12: 1K/0.1%; R0805
R13: 24K/0.1%; R0805
R14: 75K/0.1%; R0805
R16: 470R; R0805
S1, S2: JS203011_QN; JS203011
U4: LMV321; SC70-5L
U5: MAX4238/9; SO08
U6: TPS3801; DCK

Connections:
1.8V: JP14.4; also elsewhere on the board
1.8V_CPUBRD: JP15.4; also elsewhere on the board
3.3V: JP14.3; also elsewhere on the board
3.3V_CPUBRD: JP15.3; also elsewhere on the board
5V: JP14.2; also elsewhere on the board
5V_CPUBRD: JP15.2; also elsewhere on the board
+12V: JP14.1; also elsewhere on the board
+12V_CPUBRD: JP15.1; also elsewhere on the board
CURR_INPUT+: JP9.P$1, JP13.1, R6.2, S1.3, S1.5
GND: JP5.P$1; also elsewhere on the board
unnamed: R15.2, S1.7
unnamed: R15.1, U5.3 (+IN)
unnamed: R12.2, R14.1, U5.2 (-IN)
unnamed: R5.2, S1.2, S1.6
unnamed: R13.1, R14.2
unnamed: R4.I1, S1.4
unnamed: R13.2, R21.1, U5.6 (OUT)
unnamed: JP19.P$1, JP20.1, R21.2
unnamed: JP7.1, JP8.P$1
unnamed: JP6.P$1, JP7.2
unnamed: R2.1, U4.3 (-IN), U4.4 (OUT)
unnamed: R1.1, R3.2, U4.1 (+IN)
unnamed: R16.1, U6.3 (!RESET)
unnamed: S2.6, U6.4 (VDD), U6.5 (SENSE)
unnamed: D2.A, R16.2
unnamed: JP18.+, S2.3, S2.7
unnamed: JP10.P$1, JP13.2, R4.I2, R5.1, R6.1
unnamed: R4.V1, S1.8
V+: C5.1, C10.1, R1.2, S2.2, S2.4, U4.5 (V+), U5.1 (!SHUTDOWN), U5.7 (V+)
V-: C5.2, C11.1, D2.C, JP18.-, R3.1, U4.2 (V-), U5.4 (V-), U6.2 (GND)
VGND: C10.2, C11.2, JP20.2, JP21.P$1, R2.2, R4.V2, R12.1
V_EXT: JP3.P$1, JP16.1, JP16.2, JP16.3, JP16.4; also elsewhere on the board

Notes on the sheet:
+IN
-IN
Voltage output
µCurrent
OFF
ON-LED
+OUT
-OUT

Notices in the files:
parts and their libraries:
con-headers-jp: Copyright (C) 2008, Bob Starr
supressor: Copyright (C) 2009, Bob Starr
SparkFun-Connectors: Licensing: CC v3.0 Share-Alike You are welcome to use this library for commercial purposes.
